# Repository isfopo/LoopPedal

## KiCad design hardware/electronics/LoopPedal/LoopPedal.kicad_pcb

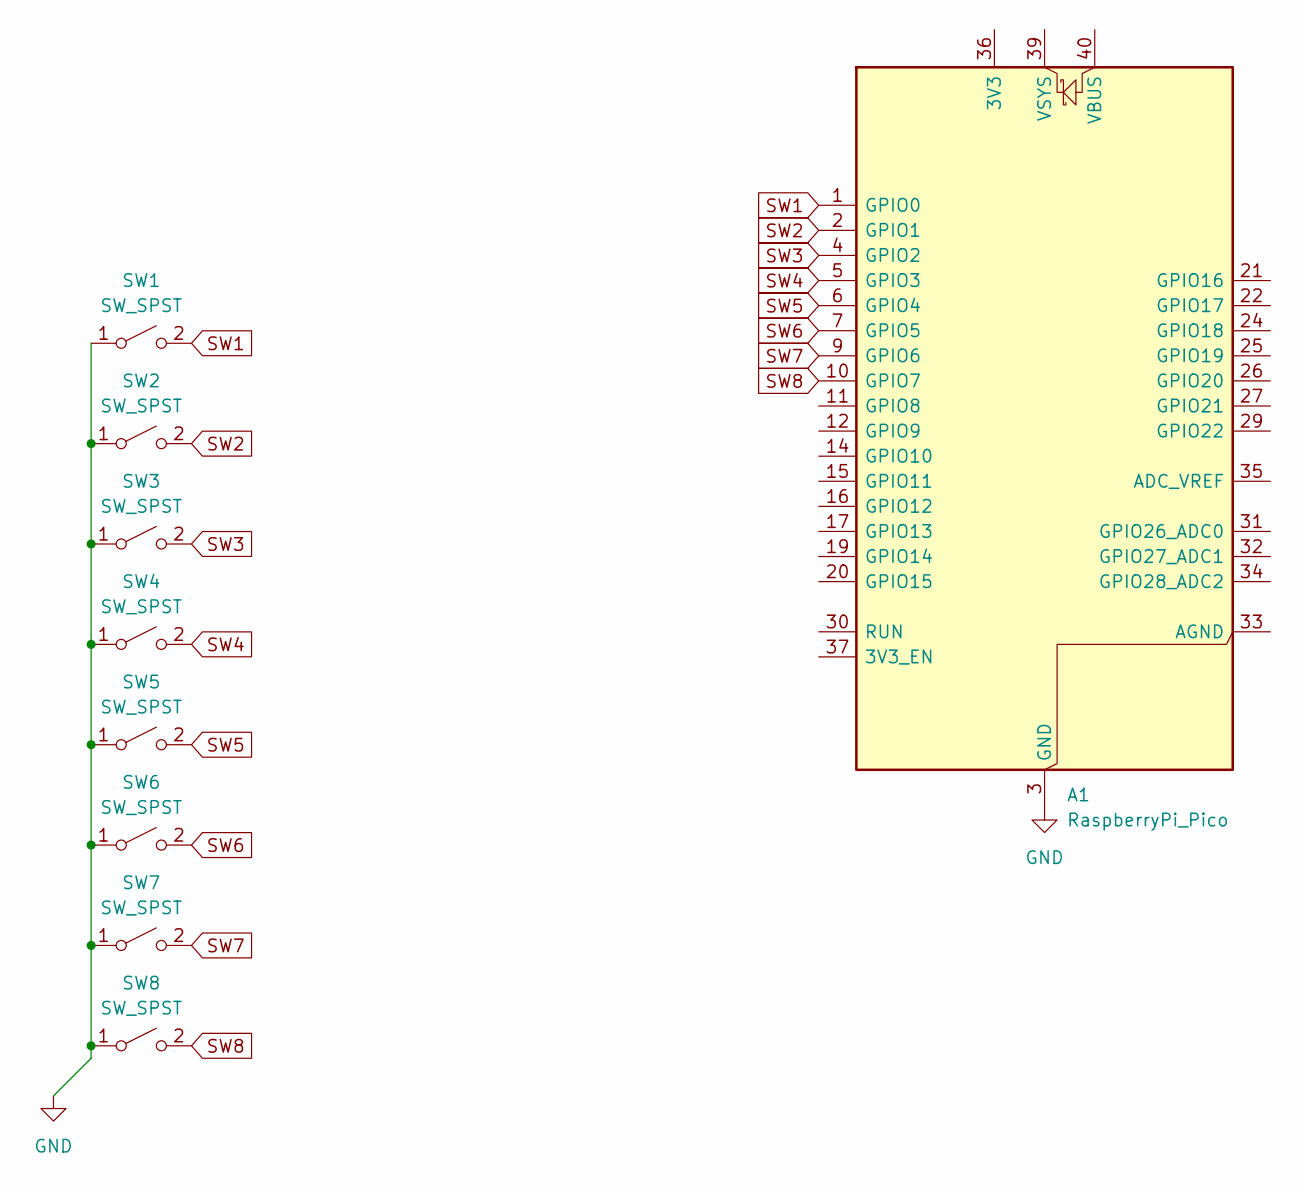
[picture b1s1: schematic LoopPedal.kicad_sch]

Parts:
A1: RaspberryPi_Pico; RaspberryPi_Pico_Common
SW1, SW2, SW3, SW4, SW5, SW6, SW7, SW8: SW_SPST; JST_PH_B2B-PH-K_1x02_P2.00mm_Vertical

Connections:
GND: A1.3 (GND), A1.8 (GND), A1.13 (GND), A1.18 (GND), A1.23 (GND), A1.28 (GND), A1.38 (GND), SW1.1 (A), SW2.1 (A), SW3.1 (A), SW4.1 (A), SW5.1 (A), SW6.1 (A), SW7.1 (A), SW8.1 (A)
SW1: A1.1 (GPIO0), SW1.2 (B)
SW2: A1.2 (GPIO1), SW2.2 (B)
SW3: A1.4 (GPIO2), SW3.2 (B)
SW4: A1.5 (GPIO3), SW4.2 (B)
SW5: A1.6 (GPIO4), SW5.2 (B)
SW6: A1.7 (GPIO5), SW6.2 (B)
SW7: A1.9 (GPIO6), SW7.2 (B)
SW8: A1.10 (GPIO7), SW8.2 (B)

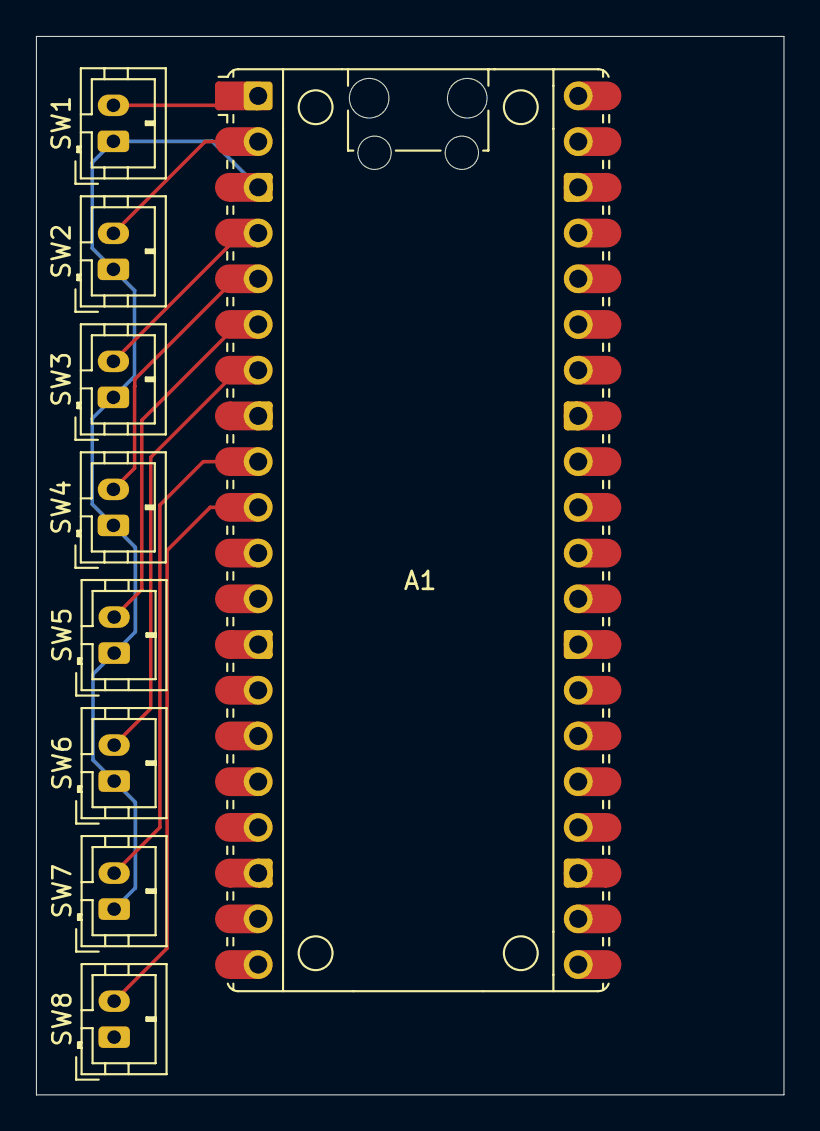
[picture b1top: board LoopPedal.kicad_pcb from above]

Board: 2 copper layers, 41.5 x 58.8 mm, 9 parts (0 on the bottom side), 9 nets.

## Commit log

2024-11-20 init
2024-11-20 ✨ feat(embedded): add initial embedded project setup
    - create Cargo.toml and Cargo.lock for project dependencies management
    - setup .cargo/config.toml with build and environment configurations
    - introduce rust-toolchain.toml to specify nightly Rust version and target
    - implement basic LED blink functionality in src/main.rs with async executor
2024-11-20 ♻️ refactor(LoopPedal): move disconnect method
    - relocate disconnect method for better code organization
    - ensure consistent method placement within class
2024-11-21 ♻️ refactor(justfile): update path and arguments for scripts
    - change path from scripts to runners for install and watch
    - update arguments passed to runners/watch.py
    ♻️ refactor(install.py): improve string formatting and logic
    - switch from single to double quotes for better consistency
    - update logic for userScriptsPath and outputDir
    ♻️ refactor(watch.py): enhance usability and script clarity
2024-11-21 updates cargo.lock
2024-11-21 ♻️ refactor(LoopPedal): enhance typing and method functionality
    - import List from typing for better type hinting
    - refactor _load_MIDI_map to _load_mappings for clarity
    - add song and tracks methods for improved song track retrieval
2024-11-21 ✨ feat(looptrack): add looptrack class with basic attributes
    - introduce new LoopTrack class with 'mode', 'track', and 'button' attributes
    - set default mode to 'stop' in the constructor
    ♻️ refactor(looppedal): enhance track handling logic
    - add property decorator to 'tracks' for better encapsulation
    - implement '_find_loop_tracks' to filter tracks by name prefix "Looper"
2024-11-22 ✨ feat(LoopPedal): add loop track initialization
    - import LoopTrack module
    - add loop_tracks attribute for managing loop tracks
    - implement init_loop_tracks method to initialize LoopTracks based on tracks with "Looper" in their names
    ♻️ refactor(LoopPedal): re-order mapping and initialization
    - reorder _load_mappings call for better readability
    - remove duplicate or misplaced code lines in _load_mappings method
2024-11-22 ✨ feat(looptrack): add long press functionality to button
    - introduce long_press_duration parameter to manage button press duration
    - add on_button_value method to handle button press and release events
    - implement on_button_press and on_button_long_press stubs for future use
2024-11-22 📝 docs(LoopTrack): add docstring to LoopTrack class constructor
    - provide detailed parameter descriptions for LoopTrack constructor
    - explain default value for long_press_duration
    ♻️ refactor(LoopTrack): enhance button press handling logic
    - add conditional structure for handling different modes in on_button_press method
2024-11-23 ♻️ refactor(looptrack): enhance loop track handling
    - refactor LoopTrack to include song and manage duplicate tracks
    - update arm method to operate on the original track
    - add duplicate_tracks list to keep track of created tracks
    ✨ feat(looptrack): introduce track duplication on recording
    - add logic for track duplication during record and overdub modes
    - implement loop end listener to manage track duplication cycle
2024-11-23 ✨ feat(looptrack): add mode transitions and new constants
    - implement mode transitions in on_button_press method to enhance functionality
    - add POST_RECORD_MODE for flexible loop control
    📝 docs(consts): add post record mode constant
    - include new POST_RECORD_MODE constant for readability and reuse
2024-11-23 ✨ feat(looptrack): enhance loop track functionality
    - add active_clip attribute to track the recording clip
    - implement automatic arming and recording initiation
    ♻️ refactor(looptrack): simplify track arming logic
    - move arming functionality to a separate module
    🔧 chore(helpers): add helper functions for track operations
    - add arm function to handle track arming logic
2024-11-23 ✨ feat(track): add track duplication feature
    - implement unarm function to disarm tracks
    - add duplicate_track function to duplicate tracks within a song
    - enhance LoopTrack functionality to duplicate and unarm tracks after recording
2024-11-24 🐛 fix(looptrack): correct track duplication and arm behavior
    - ensure duplicated tracks are properly armed and fired
    - set up loop end listener correctly on the active clip
    ✨ feat(tracks): return duplicated track object
    - add return type to duplicate_track function for improved usability
    - modify function to return the newly duplicated track object
    ♻️ refactor(tracks): update typing imports for callable support
2024-11-24 ✨ feat(looptrack): enhance track handling and duplication
    - modularize track creation and duplication logic into separate function
    - add function to retrieve track from clip for efficient track management
    ♻️ refactor(looptrack): clean up mode processing logic
    - simplify mode transitions by using new helper functions
    - remove redundant code by extracting common operations into separate methods
2024-11-24 ♻️ refactor(LoopPedal): remove unused import
    - delete import of SliderElement to clean up code and improve readability.
2024-11-25 ♻️ refactor(watch): remove redundant condition in log printing
    - remove "RemoteScript" condition check to simplify code logic
    ♻️ refactor(LoopPedal): improve looper track initialization
    - use LOOPER_TRACK_IDENTIFIER for consistent track name checks
    - replace manual superclass initialization with super()
    - remove unused note map from initialization
    ✨ feat(LoopTrack): add parse_track_options method
2024-11-25 🔥 chore(embedded): remove obsolete embedded directory
    - delete embedded .cargo/config.toml for build configuration cleanup
    - remove embedded Cargo.lock and Cargo.toml for package management cleanup
    - delete obsolete embedded rust-toolchain.toml for toolchain configuration cleanup
    - remove embedded/src/main.rs for source code cleanup
2024-11-26 👷 ci(workflows): add CI workflow for building and linting
    - set up GitHub Actions workflow for CI checks on push and pull requests
    - include build, lint, and format jobs for multiple Rust toolchains and OSes
    🔧 chore(gitignore): update gitignore for new files and directories
    - add /.pio to gitignore for generated files
    - add gitignore for embedded project in embedded/.gitignore
    📦 build(embedded): add configuration files for embedded setup
2024-11-26 adds kicad project
2024-11-26 🔧 chore(gitignore): update .gitignore file
    - remove /.pio and .vscode entries
    - clean up unnecessary ignore patterns
    🔧 chore(vscode): add VSCode configuration files
    - introduce launch.json for debug configuration
    - add settings.json with rust analyzer and spell checker settings
2024-11-27 adds pi pico and connectors
2024-11-27 📝 docs(electronics): add README.md file for electronics directory
    - create an empty README.md file for the electronics sub-directory
    🔧 chore(vscode): update spellcheck words in settings
    - add "jscad" to cSpell.words for enhanced code suggestion accuracy
    📦 build(enclosure): initialize enclosure project
    - add package.json with necessary scripts and dependencies for enclosure
    - create package-lock.json reflecting the initial dependency tree
2024-11-27 ✨ feat(enclosure): add unit conversion functionality
    - import and configure 'convert' module for unit conversion
    - initialize constants for rod, buttons, and dimensions with conversions
    📦 build(dependencies): include 'convert' package
    - add 'convert' to package.json and package-lock.json for unit conversion functionality
2024-11-27 ✨ feat(enclosure): add new body shape with extrusion
    - import arc, circle, extrudeLinear, and expand for modeling
    - calculate section width based on rod length
    - update body shape using extrusion with arc expansion
    ♻️ refactor(enclosure): update dimensions and main function
    - change dimension angle and thickness for precision
    - replace cube with body function for enhanced modeling
2024-11-27 ✨ feat(enclosure): implement end section geometry calculation
    - add new SectionOptions interface for section customization
    - introduce sectionGeo function to generate section geometry
    - enhance geometry with line and arc primitives
    ♻️ refactor(enclosure): adjust rod diameter and section width calculation
    - update rod diameter conversion to 1/2 inch
    - modify section width calculation to consider end sections
2024-11-28 ✨ feat(enclosure): add button geometry to section design
    - incorporate cylinders for button placements
    - update button and section dimensions for improved design
    ♻️ refactor(enclosure): restructure button handling and dimensions
    - adjust button properties and positioning logic
    - separate button geometry into a dedicated function
2024-11-28 ♻️ refactor(enclosure): streamline offset radius calculation
    - introduce offsetRadius variable for clarity and reuse
    - replace repeated calculations with offsetRadius variable
2024-11-28 ♻️ refactor(enclosure): rename index.ts to LoopPedalEnclosure.ts
    - rename index.ts to LoopPedalEnclosure.ts for better clarity
    - update main and scripts paths in package.json to reflect the file rename
2024-11-29 ♻️ refactor(enclosure): improve section handling and width calculation
    - remove unused import 'circle' from primitives
    - change isEndSection type to a specific string type for clarity
    - add 'hasPort' property to SectionOptions for extended functionality
    - modify width calculation to separate constants and adjusted values for end sections
    - update geometry calculations to reflect new width adjustments and end section specifications
2024-11-29 ✨ feat(enclosure): enhance LoopPedalEnclosure geometry
    - add circle primitive for improved shape creation
    - increase thickness for better structural integrity
    - modify shafts function to support both inner and outer radius
    - enhance section geometry with subtractive modeling
2024-11-29 ♻️ refactor(enclosure): improve type safety and geometry handling
    - import Geom2 type for enhanced type safety
    - refactor expand calls for clearer union of geometry elements
2024-11-30 ✨ feat(enclosure): add port geometry to loop pedal
    - introduce port diameter calculation in mm
    - add port geometry to section geometry
    - update button height for enclosure thickness change
2024-11-30 🐛 fix(enclosure): correct back dimension conversion
    - adjust back dimension from 2 to 2.5 inches for accuracy
2024-11-30 ✨ feat(justfile): add dev-enclosure command
    - introduce dev-enclosure command to start enclosure in development mode
    - ensure seamless transition to hardware/enclosure directory and execution
2024-12-01 removes embedded files
2024-12-01 📝 docs(include): add README for project header files
    - provide guidance on using header files in the project
    - link to official GCC documentation for further reading
    📝 docs(test): add README for PlatformIO test runner
    - explain purpose of the test directory
    - emphasize the importance of unit testing
    - link to PlatformIO documentation for unit testing
